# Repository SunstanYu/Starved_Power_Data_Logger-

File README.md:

# Starved Power Data Logger

ESP32-S3 data logger for low-power sensor collection with SD card storage and a local Wi-Fi display mode. The firmware samples soil moisture, DHT11 temperature/humidity, AS7343 spectral channels, and battery voltage, then appends periodic records to a single SD card log file.

## Hardware Target

- Board: Adafruit Feather ESP32-S3 No PSRAM
- Framework: Arduino through PlatformIO
- Storage: SPI SD card by default
- Sensors:
  - DHT11 temperature/humidity sensor
  - Analog soil moisture sensor
  - SparkFun AS7343 spectral sensor over I2C
- Battery monitor: ADC voltage divider, expected 200k upper / 100k lower

## Pin Map

| Function | Pin |
| --- | --- |
| Mode switch | GPIO5 |
| DHT11 data | A3 |
| Soil moisture ADC | A4 |
| Battery ADC | A2 |
| SD card CS | T12 |
| Battery LED | T13 |
| Peripheral switch 1 | T10 |
| Peripheral switch 2 | T6 |
| Peripheral switch 3 | T9 |
| AS7343 I2C SDA | GPIO3 |
| AS7343 I2C SCL | GPIO4 |

The SD card uses the board's default SPI pins. Only CS is configured explicitly.

## Operating Modes

GPIO5 selects the runtime mode:

- LOW: logger mode
- HIGH: local display mode

In logger mode, the device samples sensors, records data periodically, then enters timed deep sleep. GPIO5 is also configured as an EXT0 wake source, so driving GPIO5 HIGH can wake the device into display mode.

In display mode, the ESP32-S3 starts a local Wi-Fi access point and serves a dashboard from the device.

Display access point:

- SSID: `ESP32S3-Gateway`
- Password: `12345678`
- URL: `http://192.168.10.1/`

To leave display mode, hold GPIO5 LOW for 5 seconds. The firmware restarts and returns to logger mode.

## Sampling and Storage

Current logger timing:

- Awake window: 20 seconds
- Deep sleep duration: 10 seconds
- Record interval: every 50 samples

Storage mode is currently SD card:

```cpp
const int STORAGE_MODE = 0;
```

The SD card is initialized with a conservative SPI frequency:

```cpp
SD.begin(SDcardPin, SPI, 1000000);
```

Records are appended to:

```text
/sensor_log.txt
```

## Log Format

Each record is one line of comma-separated `key=value` fields:

```text
time_ms=23034,time=2027-02-13 01:31:08,sensor=Soil moisture + DHT11 + AS7343,sample_count=100,moisture=4095,voltage_mv=4670,temp_c=24.1,humidity=23.0,spectral=0|0|0|0|0|2|0|0|0|0|0|2|0|0|0|0|0|2
```

Fields:

- `time_ms`: milliseconds since the current boot
- `time`: system time if the ESP32 time source is valid
- `sensor`: sensor stack label
- `sample_count`: retained sample counter
- `moisture`: raw ADC reading from the soil moisture sensor
- `voltage_mv`: calculated battery voltage in millivolts
- `temp_c`: DHT11 temperature in Celsius, or `nan` on failed read
- `humidity`: DHT11 relative humidity, or `nan` on failed read
- `spectral`: AS7343 channel values separated by `|`

Note: `time_ms` resets after deep sleep because the chip restarts. The `time` field is only trustworthy after a valid time source is configured.

## Battery Voltage Calculation

The firmware assumes a 200k / 100k divider:

```text
Vadc = Vbat / 3
Vbat = Vadc * 3
```

The calculation is:

```cpp
int raw = analogRead(batteryAdcPin);
float vadc = ((float)raw / 4095.0f) * 3.3f;
float vbat = vadc * 3.0f;
int batteryMv = (int)(vbat * 1000.0f);
```

ADC setup:

```cpp
analogReadResolution(12);
analogSetPinAttenuation(batteryAdcPin, ADC_11db);
```

The battery measurement point should be the battery positive terminal through the divider. Do not hard-wire USB/VBUS and the battery positive terminal together unless the board's power path explicitly supports that connection.

## Build and Upload

Install PlatformIO, then run:

```sh
pio run
```

Upload to the board:

```sh
pio run --target upload
```

Open the serial monitor:

```sh
pio device monitor --baud 115200
```

## Project Layout

```text
.
├── platformio.ini
├── partitions.csv
├── src
│   ├── main.cpp
│   ├── display_gateway.cpp
│   └── display_gateway.h
├── include
├── lib
└── test
```

## Notes

- `.pio` build output is ignored by Git.
- The project includes an FFat partition, but the active storage mode is SD card.
- The display dashboard reads the same storage source used by the logger.
- If the AS7343 values saturate, reduce gain or integration time in the sensor configuration.
- If soil moisture stays near 4095, verify the sensor output range and ADC wiring.

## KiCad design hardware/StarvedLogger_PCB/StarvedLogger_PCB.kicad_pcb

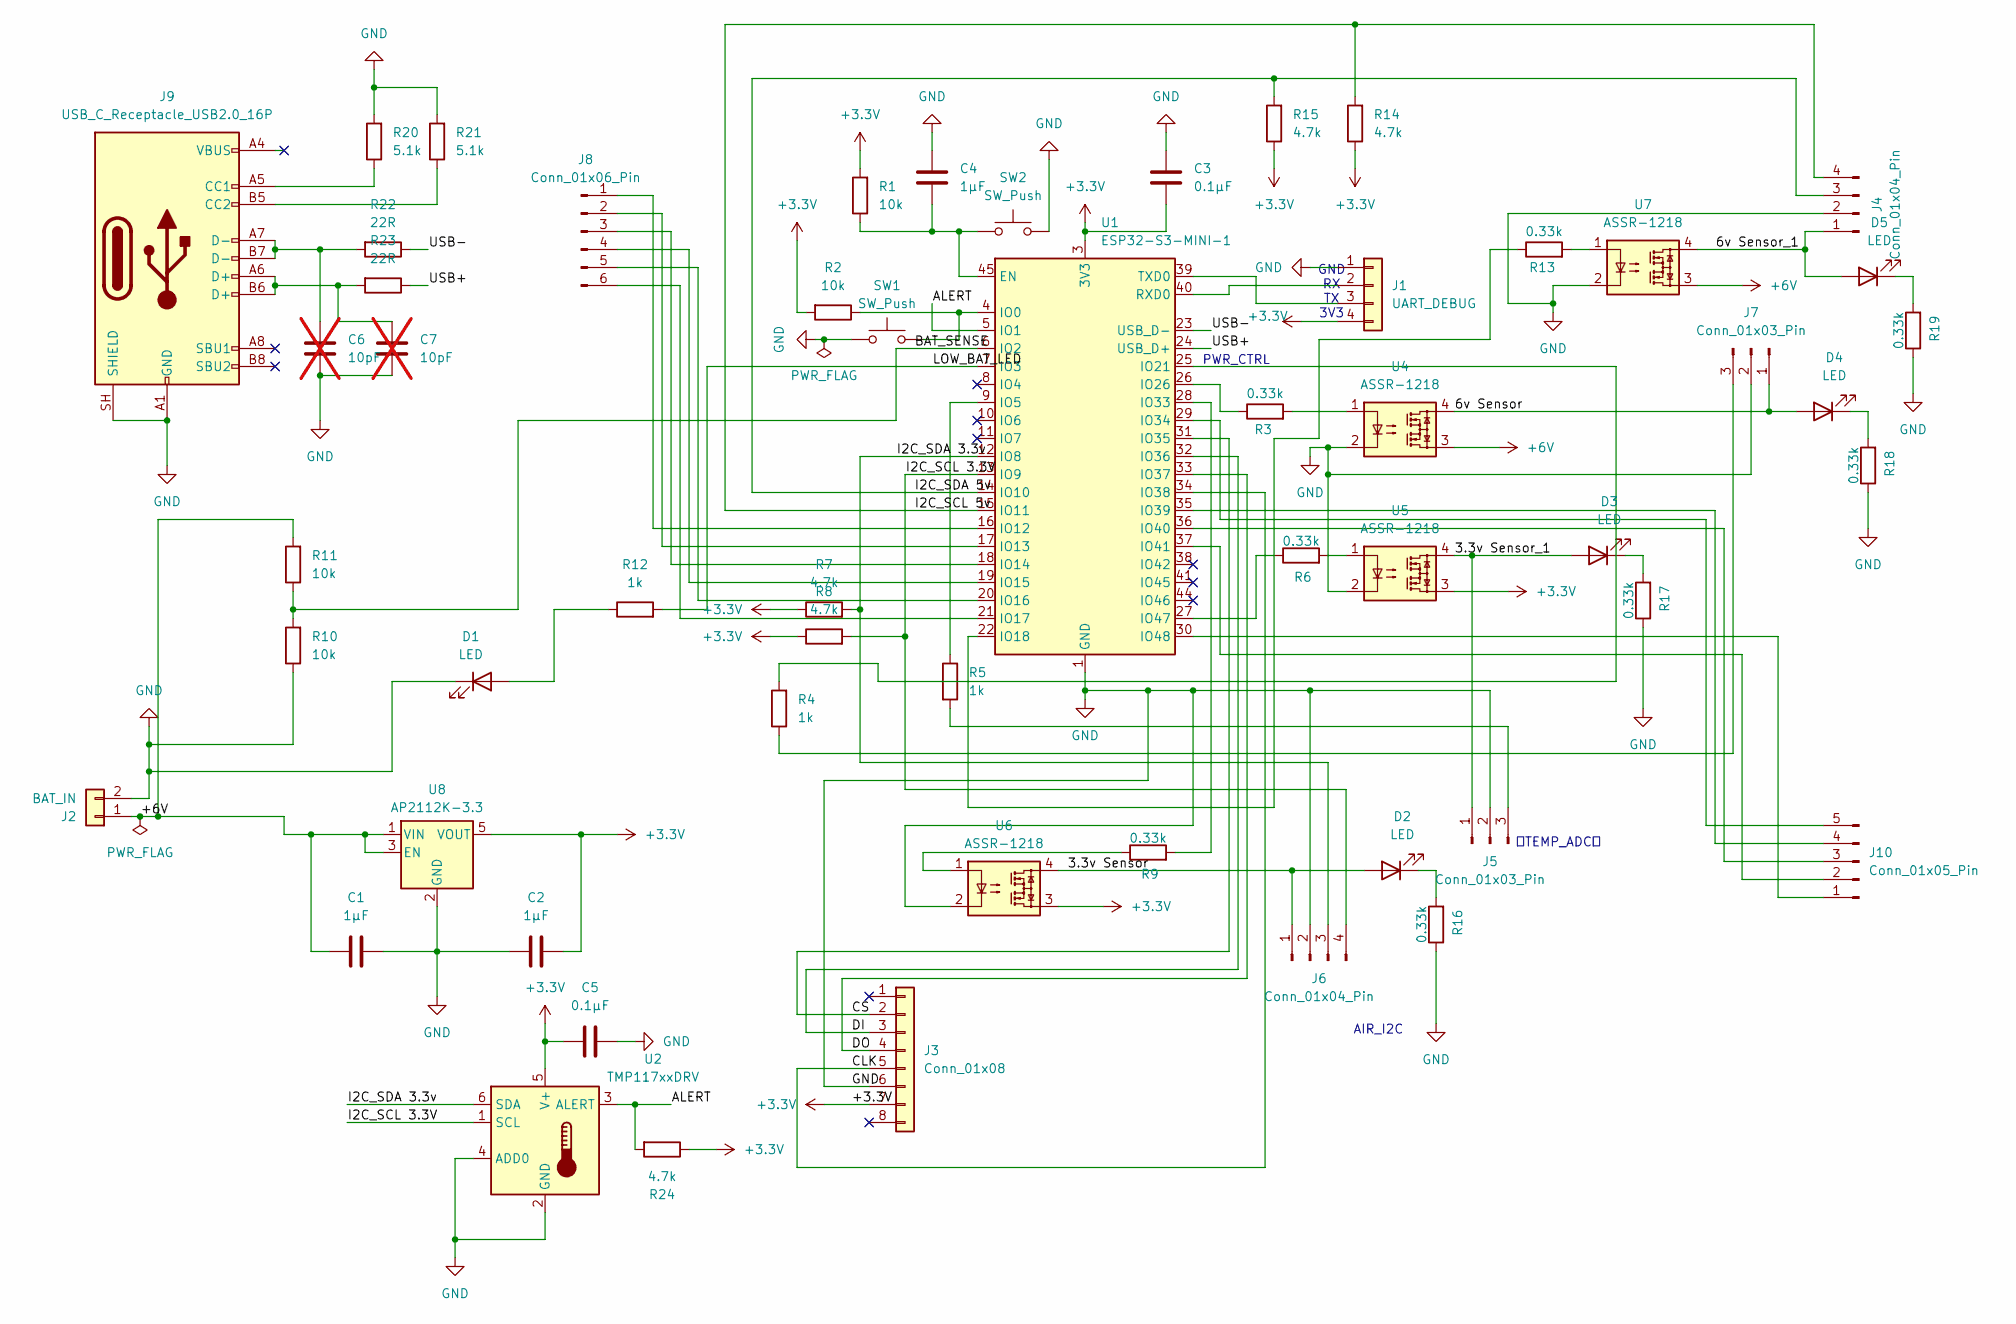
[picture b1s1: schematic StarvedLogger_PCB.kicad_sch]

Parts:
C1, C2, C4: 1µF; C_0603_1608Metric
C3, C5: 0.1µF; C_0603_1608Metric
C6, C7: 10pF; C_0603_1608Metric; not fitted
D1, D2, D3, D4, D5: LED; LED_0603_1608Metric
J1: UART_DEBUG; PinHeader_1x04_P2.54mm_Vertical
J2: BAT_IN; PinHeader_1x02_P2.54mm_Vertical
J3: Conn_01x08; PinHeader_1x08_P2.54mm_Vertical
J4, J6: Conn_01x04_Pin; PinHeader_1x04_P2.54mm_Vertical
J5, J7: Conn_01x03_Pin; PinHeader_1x03_P2.54mm_Vertical
J8: Conn_01x06_Pin; PinHeader_1x06_P2.54mm_Vertical
J9: USB_C_Receptacle_USB2.0_16P; USB_C_Receptacle_Amphenol_12401610E4-2A_CircularHoles
J10: Conn_01x05_Pin; PinHeader_1x05_P2.54mm_Vertical
R1, R2, R10, R11: 10k; R_0603_1608Metric
R3, R6, R9, R13, R16, R17, R18, R19: 0.33k; R_0603_1608Metric
R4, R5, R12: 1k; R_0603_1608Metric
R7, R8, R14, R15, R24: 4.7k; R_0603_1608Metric
R20, R21: 5.1k; R_0603_1608Metric
R22, R23: 22R; R_0603_1608Metric
SW1, SW2: SW_Push; SW_SPST_TL3342
U1: ESP32-S3-MINI-1
U2: TMP117xxDRV; WSON-6-1EP_2x2mm_P0.65mm_EP1x1.6mm
U4, U5, U6, U7: ASSR-1218; SO-4_4.4x4.3mm_P2.54mm
U8: AP2112K-3.3; SOT-23-5

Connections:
+3.3V: C2.2, C3.2, C5.1, J1.4, J3.7, R1.2, R2.2, R7.1, R8.1, R14.1, R15.1, R24.1, U1.3 (3V3), U2.5 (V+), U5.3, U6.3, U8.5 (VOUT)
+6V: C1.1, J2.1, R11.2, U4.3, U7.3, U8.1 (VIN), U8.3 (EN)
/3.3v Sensor: D2.2 (A), J6.1, U6.4
/3.3v Sensor_1: D3.2 (A), J5.1, U5.4
/6v Sensor: D4.2 (A), J7.1, U4.4
/6v Sensor_1: D5.2 (A), J4.1, U7.4
/ALERT: R24.2, U1.5 (IO1), U2.3 (ALERT)
/BAT_SENSE: R10.2, R11.1, U1.6 (IO2)
/CLK: J3.5, U1.34 (IO38)
/CS: J3.2, U1.31 (IO35)
/DI: J3.3, U1.32 (IO36)
/DO: J3.4, U1.33 (IO37)
/I2C_SCL 3.3V: J6.4, R8.2, U1.13 (IO9), U2.1 (SCL)
/I2C_SCL 5v: J4.4, R14.2, U1.15 (IO11)
/I2C_SDA 3.3v: J6.3, R7.2, U1.12 (IO8), U2.6 (SDA)
/I2C_SDA 5v: J4.3, R15.2, U1.14 (IO10)
/LOW_BAT_LED: R12.2, U1.7 (IO3)
/USB+: R23.1, U1.24 (USB_D+)
/USB-: R22.1, U1.23 (USB_D-)
GND: C1.2, C2.1, C3.1, C4.1, C5.2, C6.1, C7.1, D1.1 (K), J1.1, J2.2, J3.6, J4.2, J5.2, J6.2, J7.2, J9.A1 (GND), J9.A12 (GND), J9.B1 (GND), J9.B12 (GND), J9.SH (SHIELD), R10.1, R16.1, R17.1, R18.1, R19.1, R20.2, R21.2, SW1.1, SW2.2, U1.1 (GND), U1.2 (GND), U1.42 (GND), U1.43 (GND), U1.46 (GND), U1.47 (GND), U1.48 (GND), U1.49 (GND), U1.50 (GND), U1.51 (GND), U1.52 (GND), U1.53 (GND), U1.54 (GND), U1.55 (GND), U1.56 (GND), U1.57 (GND), U1.58 (GND), U1.59 (GND), U1.60 (GND), U1.61 (GND), U1.62 (GND), U1.63 (GND), U1.64 (GND), U1.65 (GND), U2.2 (GND), U2.4 (ADD0), U4.2, U5.2, U6.2, U7.2, U8.2 (GND)
unnamed: C6.2, J9.A7 (D-), J9.B7 (D-), R22.2
unnamed: C7.2, J9.A6 (D+), J9.B6 (D+), R23.2
unnamed: D1.2 (A), R12.1
unnamed: D2.1 (K), R16.2
unnamed: D3.1 (K), R17.2
unnamed: D4.1 (K), R18.2
unnamed: D5.1 (K), R19.2
unnamed: J1.2, U1.40 (RXD0)
unnamed: J1.3, U1.39 (TXD0)
unnamed: J5.3, R5.2
unnamed: J7.3, R4.1
unnamed: J8.1, U1.16 (IO12)
unnamed: J8.2, U1.17 (IO13)
unnamed: J8.3, U1.18 (IO14)
unnamed: J8.4, U1.19 (IO15)
unnamed: J8.5, U1.20 (IO16)
unnamed: J8.6, U1.21 (IO17)
unnamed: J9.A5 (CC1), R20.1
unnamed: J9.B5 (CC2), R21.1
unnamed: J10.1, U1.30 (IO48)
unnamed: J10.2, U1.37 (IO41)
unnamed: J10.3, U1.36 (IO40)
unnamed: J10.4, U1.35 (IO39)
unnamed: J10.5, U1.29 (IO34)
unnamed: R3.2, U4.1
unnamed: R6.2, U5.1
unnamed: R9.1, U6.1
unnamed: R13.2, U7.1
unnamed: C4.2, R1.1, SW2.1, U1.45 (EN)
unnamed: R2.1, SW1.2, U1.4 (IO0)
unnamed: R5.1, U1.9 (IO5)
unnamed: R13.1, U1.22 (IO18)
unnamed: R4.2, U1.25 (IO21)
unnamed: R3.1, U1.26 (IO26)
unnamed: R9.2, U1.28 (IO33)
unnamed: R6.1, U1.27 (IO47)

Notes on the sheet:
AIR_I2C
PWR_CTRL
GND RX TX 3V3
（TEMP_ADC）

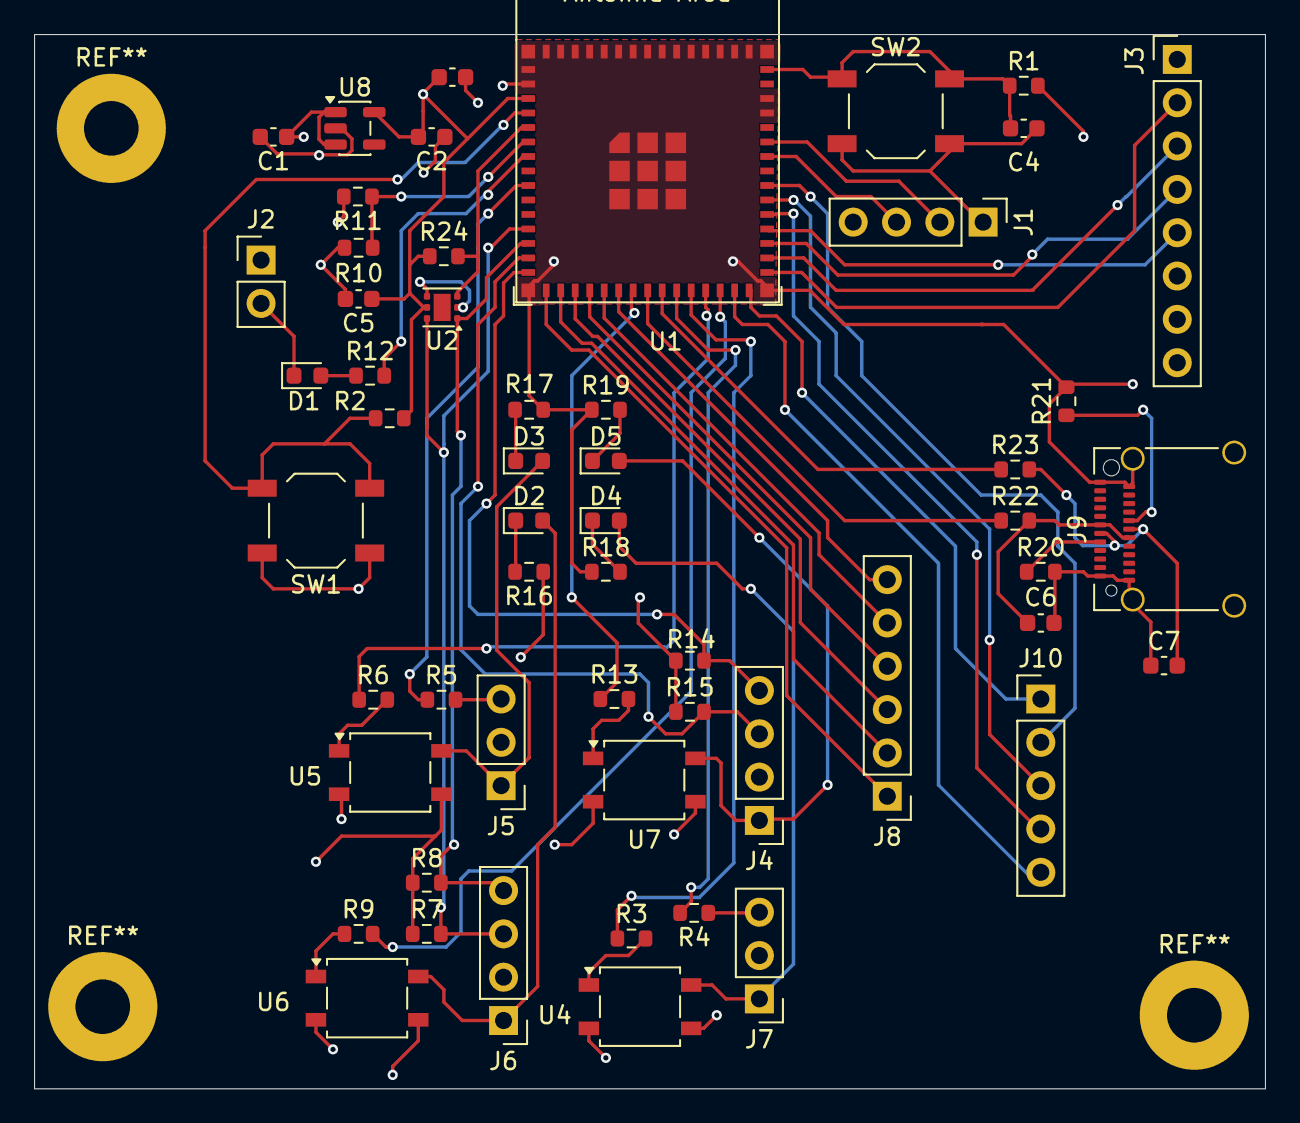
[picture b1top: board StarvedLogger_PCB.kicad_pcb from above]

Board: 4 copper layers, 72.2 x 61.8 mm, 55 parts (0 on the bottom side), 56 nets.

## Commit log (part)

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2026-05-01 Initial ESP32-S3 data logger project
